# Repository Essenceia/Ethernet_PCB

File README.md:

# PCBs for Coffee-Shop project

## Biscotti 

x1 Ethernet Pmod for full-duplex 100BASE-TX over RMII using the LAN8720A chip. 

## AI Policy 

No AI was used by me in the development of this hardware. 

All code and design decisions are, and will remain, entirely human made. 

## License 

Copyright Julia Desmazes, 2026 

This hardware is distributed under the **strongly** reciprocal CERN Open Hardware Licence Version 2 unless
otherwise specified.

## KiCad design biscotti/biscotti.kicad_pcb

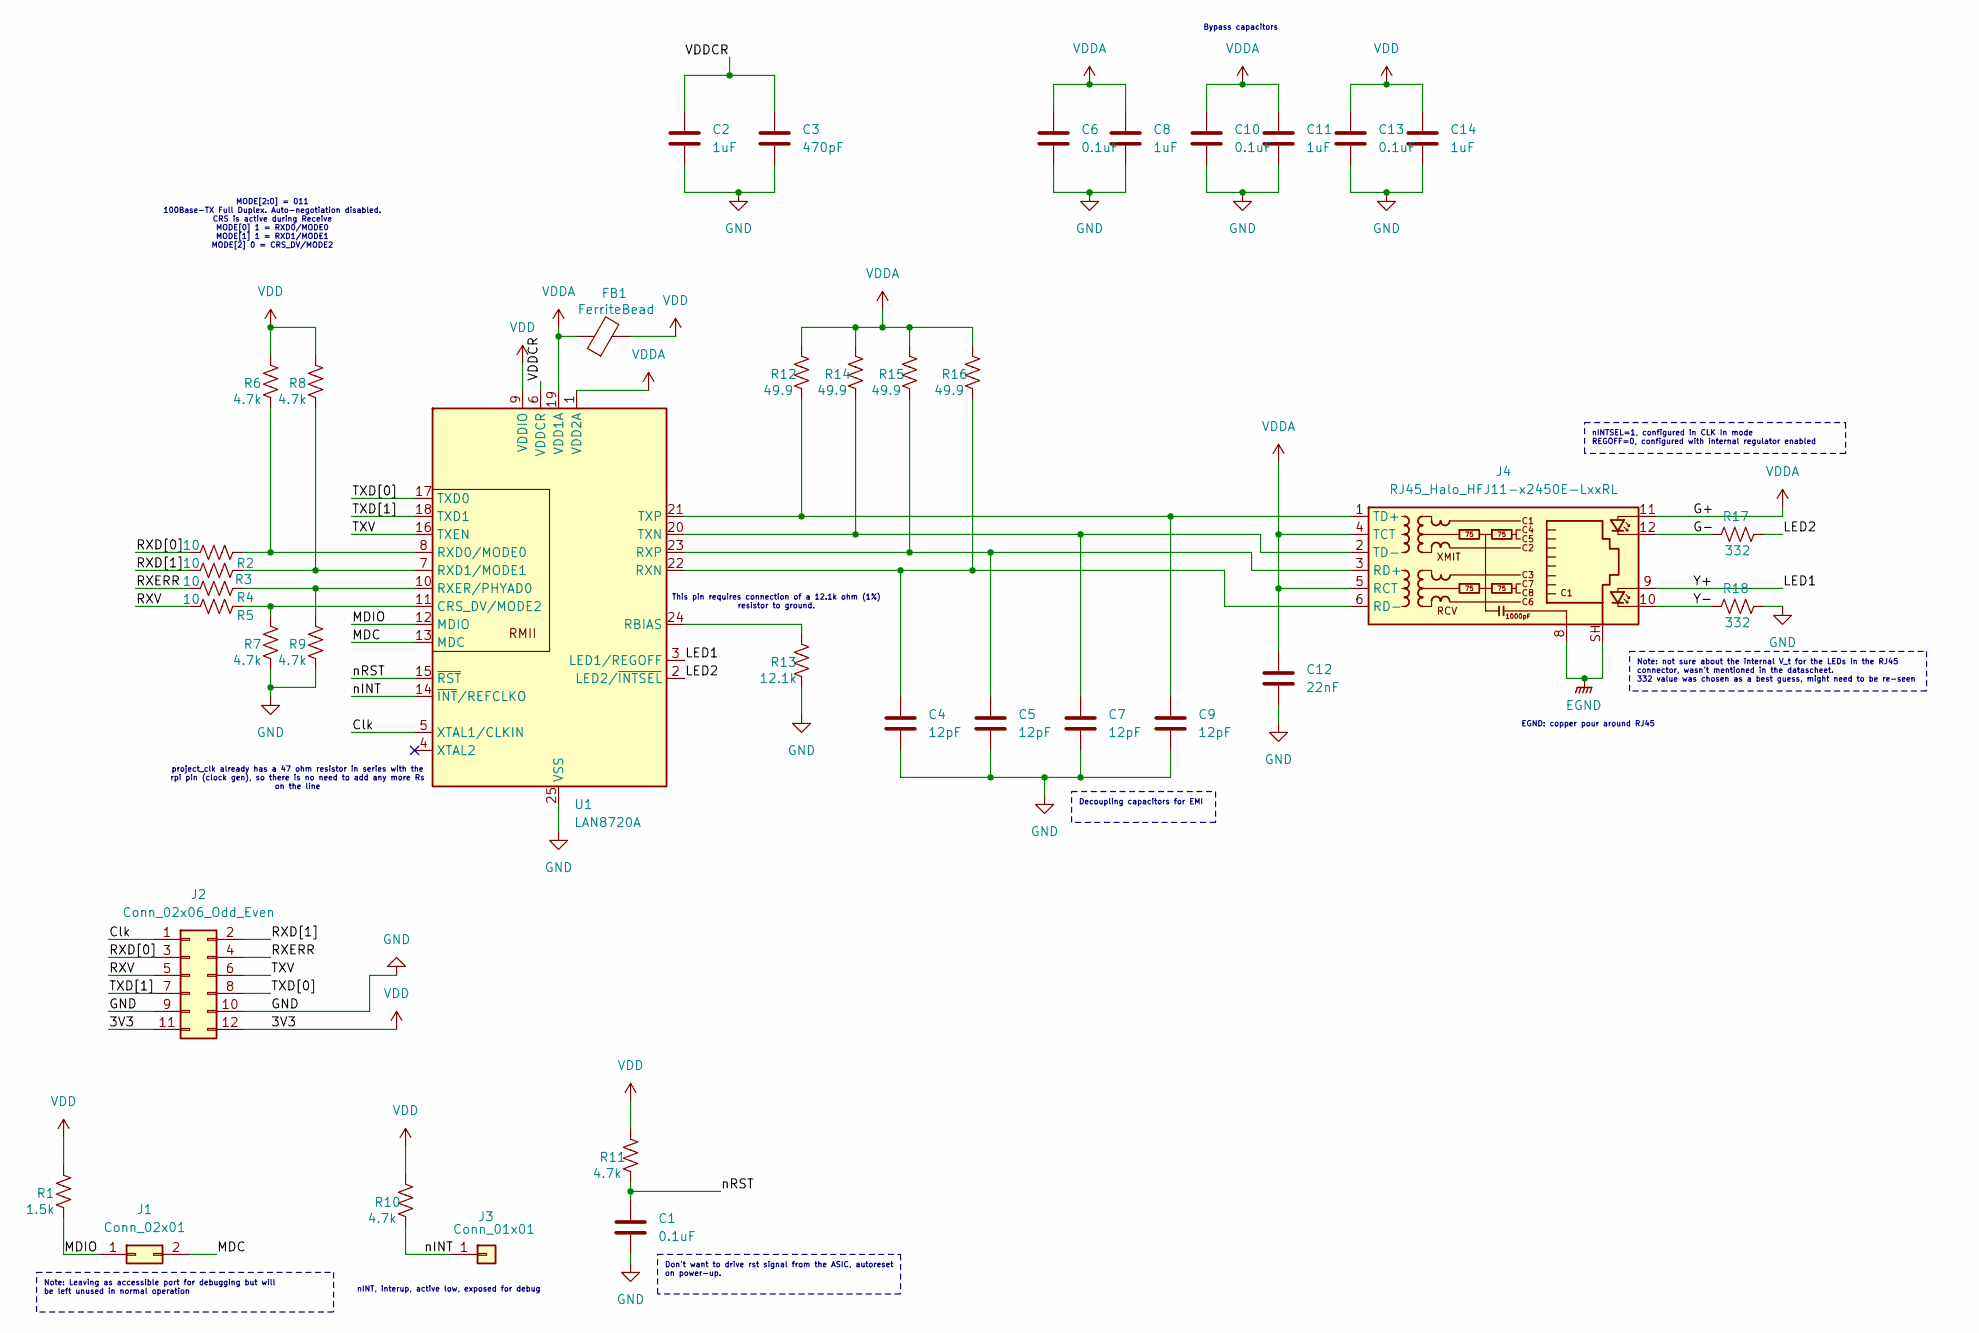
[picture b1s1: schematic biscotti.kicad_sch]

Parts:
C1, C6, C10, C13: 0.1uF; C_1206_3216Metric_Pad1.33x1.80mm_HandSolder
C2, C8, C11, C14: 1uF; C_1206_3216Metric_Pad1.33x1.80mm_HandSolder
C3: 470pF; C_1206_3216Metric_Pad1.33x1.80mm_HandSolder
C4, C5, C7, C9: 12pF; C_1206_3216Metric_Pad1.33x1.80mm_HandSolder
C12: 22nF; C_1206_3216Metric_Pad1.33x1.80mm_HandSolder
FB1: FerriteBead; L_1206_3216Metric_Pad1.22x1.90mm_HandSolder
J1: Conn_02x01; PinHeader_2x01_P2.54mm_Vertical
J2: Conn_02x06_Odd_Even; PinHeader_2x06_P2.54mm_Vertical
J3: Conn_01x01; PinHeader_1x01_P2.54mm_Vertical
J4: RJ45_Halo_HFJ11-x2450E-LxxRL; RJ45_HALO_HFJ11-x2450E-LxxRL_Horizontal
R1: 1.5k; R_1206_3216Metric_Pad1.30x1.75mm_HandSolder
R2, R3, R4, R5: 10; R_1206_3216Metric_Pad1.30x1.75mm_HandSolder
R6, R7, R8, R9, R10, R11: 4.7k; R_1206_3216Metric_Pad1.30x1.75mm_HandSolder
R12, R14, R15, R16: 49.9; R_1206_3216Metric_Pad1.30x1.75mm_HandSolder
R13: 12.1k; R_1206_3216Metric_Pad1.30x1.75mm_HandSolder
R17, R18: 332; R_1206_3216Metric_Pad1.30x1.75mm_HandSolder
U1: LAN8720A; VQFN-24-1EP_4x4mm_P0.5mm_EP2.5x2.5mm_ThermalVias

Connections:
/Clk: J2.1, U1.5 (XTAL1/CLKIN)
/G-: J4.12, R17.2
/LED1: J4.9, U1.3 (LED1/REGOFF)
/LED2: R17.1, U1.2 (LED2/~INTSEL)
/MDC: J1.2, U1.13 (MDC)
/MDIO: J1.1, R1.2, U1.12 (MDIO)
/RXD[0]: J2.3, R2.1
/RXD[1]: J2.2, R3.1
/RXERR: J2.4, R4.1
/RXV: J2.5, R5.1
/TXD[0]: J2.8, U1.17 (TXD0)
/TXD[1]: J2.7, U1.18 (TXD1)
/TXV: J2.6, U1.16 (TXEN)
/VDDCR: C2.1, C3.1, U1.6 (VDDCR)
/Y-: J4.10, R18.2
/nINT: J3.1 (Pin_1_1), R10.2, U1.14 (~INT/REFCLKO)
/nRST: C1.1, R11.2, U1.15 (~RST)
EGND: J4.8, J4.SH
GND: C1.2, C2.2, C3.2, C4.2, C5.2, C6.2, C7.2, C8.2, C9.2, C10.2, C11.2, C12.2, C13.2, C14.2, J2.9, J2.10, R7.2, R9.2, R13.2, R18.1, U1.25 (VSS)
unnamed: C5.1, J4.3 (RD+), R15.2, U1.23 (RXP)
unnamed: C4.1, J4.6 (RD-), R16.2, U1.22 (RXN)
unnamed: C9.1, J4.1 (TD+), R12.2, U1.21 (TXP)
unnamed: C7.1, J4.2 (TD-), R14.2, U1.20 (TXN)
unnamed: R5.2, R7.1, U1.11 (CRS_DV/MODE2)
unnamed: R13.1, U1.24 (RBIAS)
unnamed: R2.2, R6.2, U1.8 (RXD0/MODE0)
unnamed: R3.2, R8.2, U1.7 (RXD1/MODE1)
unnamed: R4.2, R9.1, U1.10 (RXER/PHYAD0)
VDD: C13.1, C14.1, FB1.2, J2.11, J2.12, R1.1, R6.1, R8.1, R10.1, R11.1, U1.9 (VDDIO)
VDDA: C6.1, C8.1, C10.1, C11.1, C12.1, FB1.1, J4.4 (TCT), J4.5 (RCT), J4.11, R12.1, R14.1, R15.1, R16.1, U1.1 (VDD2A), U1.19 (VDD1A)

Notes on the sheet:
This pin requires connection of a 12.1k ohm (1%) resistor to ground.
nINT, interup, active low, exposed for debug
MODE[2:0] = 011 100Base-TX Full Duplex. Auto-negotiation disabled. CRS is active during Receive MODE[0] 1 = RXD0/MODE0 MODE[1] 1 = RXD1/MODE1 MODE[2] 0 = CRS_DV/MODE2
project_clk already has a 47 ohm resistor in series with the rpi pin (clock gen), so there is no need to add any more Rs on the line
Bypass capacitors
EGND: copper pour around RJ45
Note: not sure about the internal V_t for the LEDs in the RJ45 connector, wasn't mentioned in the datascheet. 332 value was chosen as a best guess, might need to be re-seen
nINTSEL=1, configured in CLK In mode REGOFF=0, configured with internal regulator enabled
Decoupling capacitors for EMI
Don't want to drive rst signal from the ASIC, autoreset on power-up.
Note: Leaving as accessible port for debugging but will be left unused in normal operation

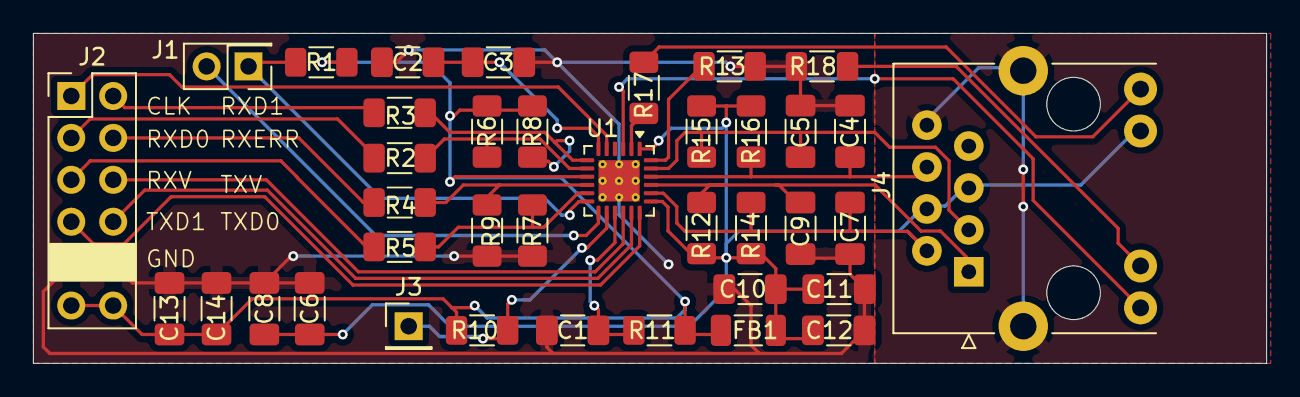
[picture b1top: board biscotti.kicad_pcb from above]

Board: 2 copper layers, 74.8 x 20.0 mm, 38 parts (0 on the bottom side), 30 nets.
